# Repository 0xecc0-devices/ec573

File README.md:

# ec573 - Amiga 500 8MB Z2 DRAM + 2 channel IDE controller

## description
The ecc0 573 - or ec573 - is an Amiga 500 internal 8MB DRAM Zorro II expansion with 2 channel autoboot IDE controller sitting under the MC68000 CPU. It does fit into a standard Amiga 500 Mainboard interfering with neither ROM nor expansion connector.

### rendered pcb

### real pcb

### fitted into A500

DRAM and IDE controller are added using Amiga autoconfig mechanism with chain snooping. The expansion requires at least Kickstart 2.04 (v37.299).

## features

 - 8MB DRAM Zorro II memory expansion
  - IDE controller with 2 channels for 4 devices using the fabulous [lide.device](https://github.com/LIV2/lide.device)
 - full Zorro II autoconfig
 - jumperless
 - 2,5" IDE connector
 - 3,5" IDE connector with +5V power supply (fused on pin 20)
 - IDE LED connector
 - 128kB IDE controller ROM with CD boot capability
 - IDE autoboot ROM in circuit flash updateable
 - compatible with Kickstart v37.299 (2.04) and later

## technical details
 - 8MB DRAM mapped into Amiga's Zorro II memory address space ($20.0000 - $9F.FFFF)
 - 128kB IDE controller mapped as I/O device into Amiga's Zorro II I/O address space
 - 15,6 &#xb5;S DRAM CBR refresh

## limitations
The ecc0 573 has been designed to achieve several goals. This leaves the finished design with limitations which are intended, yet to be made transparent.

1. Due to the absense of Amiga Zorro Autoconfig signals **cfgin** and **cfgout** on the CPU slot, a snooping mechanism waits for all other devices to be configured first. This snooping mechanism needs at least Kickstart v37.299 to work.
2. Neither DRAM nor IDE controller are deactivateable.
3. The Zorro II DRAM size is fixed to 8MB. If another autoconfig device is claiming any memory before, none of the expansion's DRAM will be available.
4. The IDE controller uses [lide.device](https://github.com/LIV2/lide.device) by Matt Harlum as autoboot firmware thus inheriting all it's limitations.
5. The expansion always configures last in the autoconfiguration chain and uses the remaining resources available.
<!--stackedit_data:
eyJoaXN0b3J5IjpbMTAzMzAxODg2NSwtMTc1ODM2NjkzMCwxMD
k5NTEyNDgxXX0=
-->

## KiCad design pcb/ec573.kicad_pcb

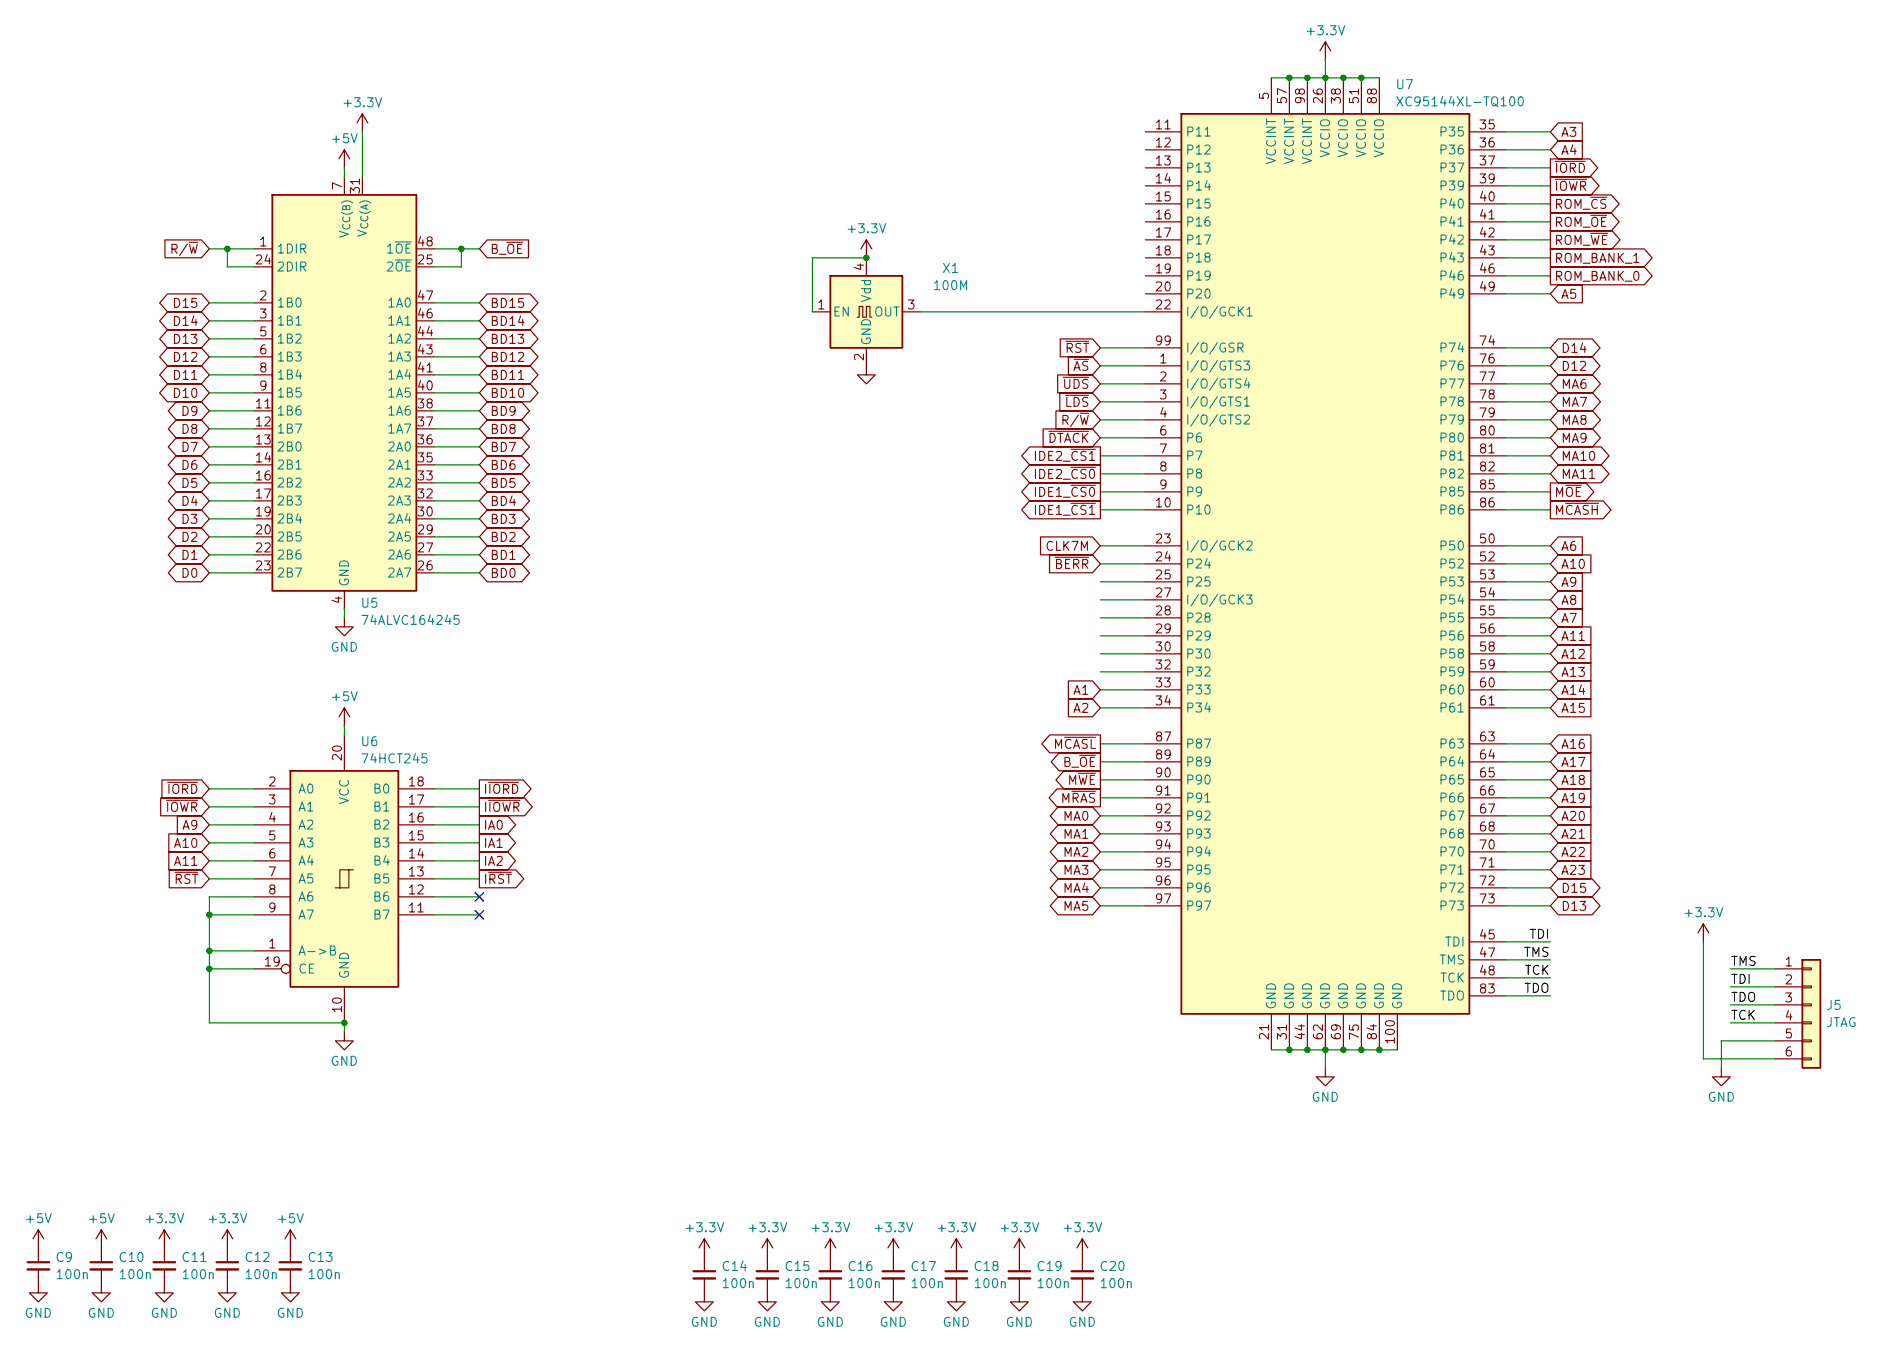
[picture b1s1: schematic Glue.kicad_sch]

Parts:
C9, C10, C11, C12, C13, C14, C15, C16, C17, C18, C19, C20: 100n; C_0603_1608Metric
J5: JTAG; PinHeader_1x06_P1.27mm_Vertical
U5: 74ALVC164245; TSSOP-48_6.1x12.5mm_P0.5mm
U6: 74HCT245; TSSOP-20_4.4x6.5mm_P0.65mm
U7: XC95144XL-TQ100; TQFP-100_14x14mm_P0.5mm
X1: 100M; Oscillator_SMD_Abracon_ASE-4Pin_3.2x2.5mm

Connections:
+3.3V: C11.1, C12.1, C14.1, C15.1, C16.1, C17.1, C18.1, C19.1, C20.1, J5.6, U5.31 (V_{CC(A)}), U5.42 (V_{CC(A)}), U7.5 (VCCINT), U7.26 (VCCIO), U7.38 (VCCIO), U7.51 (VCCIO), U7.57 (VCCINT), U7.88 (VCCIO), U7.98 (VCCINT), X1.1 (EN), X1.4 (Vdd); also elsewhere on the board
+5V: C9.1, C10.1, C13.1, U5.7 (V_{CC(B)}), U5.18 (V_{CC(B)}), U6.20 (VCC); also elsewhere on the board
/Glue/TCK: J5.4, U7.48 (TCK)
/Glue/TDI: J5.2, U7.45 (TDI)
/Glue/TDO: J5.3, U7.83 (TDO)
/Glue/TMS: J5.1, U7.47 (TMS)
A1: U7.33; also elsewhere on the board
A2: U7.34; also elsewhere on the board
A3: U7.35; also elsewhere on the board
A4: U7.36; also elsewhere on the board
A5: U7.49; also elsewhere on the board
A6: U7.50; also elsewhere on the board
A7: U7.55; also elsewhere on the board
A8: U7.54; also elsewhere on the board
A9: U6.4 (A2), U7.53; also elsewhere on the board
A10: U6.5 (A3), U7.52; also elsewhere on the board
A11: U6.6 (A4), U7.56; also elsewhere on the board
A12: U7.58; also elsewhere on the board
A13: U7.59; also elsewhere on the board
A14: U7.60; also elsewhere on the board
A15: U7.61; also elsewhere on the board
A16: U7.63; also elsewhere on the board
A17: U7.64; also elsewhere on the board
A18: U7.65; also elsewhere on the board
A19: U7.66; also elsewhere on the board
A20: U7.67; also elsewhere on the board
A21: U7.68; also elsewhere on the board
A22: U7.70; also elsewhere on the board
A23: U7.71; also elsewhere on the board
BD0: U5.26 (2A7); also elsewhere on the board
BD1: U5.27 (2A6); also elsewhere on the board
BD2: U5.29 (2A5); also elsewhere on the board
BD3: U5.30 (2A4); also elsewhere on the board
BD4: U5.32 (2A3); also elsewhere on the board
BD5: U5.33 (2A2); also elsewhere on the board
BD6: U5.35 (2A1); also elsewhere on the board
BD7: U5.36 (2A0); also elsewhere on the board
BD8: U5.37 (1A7); also elsewhere on the board
BD9: U5.38 (1A6); also elsewhere on the board
BD10: U5.40 (1A5); also elsewhere on the board
BD11: U5.41 (1A4); also elsewhere on the board
BD12: U5.43 (1A3); also elsewhere on the board
BD13: U5.44 (1A2); also elsewhere on the board
BD14: U5.46 (1A1); also elsewhere on the board
BD15: U5.47 (1A0); also elsewhere on the board
B_~OE: U5.25 (2~OE), U5.48 (1~OE), U7.89
CLK7M: U7.23 (I/O/GCK2); also elsewhere on the board
D0: U5.23 (2B7); also elsewhere on the board
D1: U5.22 (2B6); also elsewhere on the board
D2: U5.20 (2B5); also elsewhere on the board
D3: U5.19 (2B4); also elsewhere on the board
D4: U5.17 (2B3); also elsewhere on the board
D5: U5.16 (2B2); also elsewhere on the board
D6: U5.14 (2B1); also elsewhere on the board
D7: U5.13 (2B0); also elsewhere on the board
D8: U5.12 (1B7); also elsewhere on the board
D9: U5.11 (1B6); also elsewhere on the board
D10: U5.9 (1B5); also elsewhere on the board
D11: U5.8 (1B4); also elsewhere on the board
D12: U5.6 (1B3), U7.76; also elsewhere on the board
D13: U5.5 (1B2), U7.73; also elsewhere on the board
D14: U5.3 (1B1), U7.74; also elsewhere on the board
D15: U5.2 (1B0), U7.72; also elsewhere on the board
GND: C9.2, C10.2, C11.2, C12.2, C13.2, C14.2, C15.2, C16.2, C17.2, C18.2, C19.2, C20.2, J5.5, U5.4 (GND), U5.10 (GND), U5.15 (GND), U5.21 (GND), U5.28 (GND), U5.34 (GND), U5.39 (GND), U5.45 (GND), U6.1 (A->B), U6.8 (A6), U6.9 (A7), U6.10 (GND), U6.19 (CE), U7.21 (GND), U7.31 (GND), U7.44 (GND), U7.62 (GND), U7.69 (GND), U7.75 (GND), U7.84 (GND), U7.100 (GND), X1.2 (GND); also elsewhere on the board
IA0: U6.16 (B2); also elsewhere on the board
IA1: U6.15 (B3); also elsewhere on the board
IA2: U6.14 (B4); also elsewhere on the board
IDE1_~CS0: U7.9; also elsewhere on the board
IDE1_~CS1: U7.10; also elsewhere on the board
IDE2_~CS0: U7.8; also elsewhere on the board
IDE2_~CS1: U7.7; also elsewhere on the board
I~IORD: U6.18 (B0); also elsewhere on the board
I~IOWR: U6.17 (B1); also elsewhere on the board
I~RST: U6.13 (B5); also elsewhere on the board
MA0: U7.92; also elsewhere on the board
MA1: U7.93; also elsewhere on the board
MA2: U7.94; also elsewhere on the board
MA3: U7.95; also elsewhere on the board
MA4: U7.96; also elsewhere on the board
MA5: U7.97; also elsewhere on the board
MA6: U7.77; also elsewhere on the board
MA7: U7.78; also elsewhere on the board
MA8: U7.79; also elsewhere on the board
MA9: U7.80; also elsewhere on the board
MA10: U7.81; also elsewhere on the board
MA11: U7.82; also elsewhere on the board
M~CASH: U7.86; also elsewhere on the board
M~CASL: U7.87; also elsewhere on the board
M~OE: U7.85; also elsewhere on the board
M~RAS: U7.91; also elsewhere on the board
M~WE: U7.90; also elsewhere on the board
unnamed: U7.22 (I/O/GCK1), X1.3 (OUT)
ROM_BANK_0: U7.46; also elsewhere on the board
ROM_BANK_1: U7.43; also elsewhere on the board
ROM_~CS: U7.40; also elsewhere on the board
ROM_~OE: U7.41; also elsewhere on the board
ROM_~WE: U7.42; also elsewhere on the board
R/~W: U5.1 (1DIR), U5.24 (2DIR), U7.4 (I/O/GTS2); also elsewhere on the board
~AS: U7.1 (I/O/GTS3); also elsewhere on the board
~BERR: U7.24; also elsewhere on the board
~DTACK: U7.6; also elsewhere on the board
~IORD: U6.2 (A0), U7.37
~IOWR: U6.3 (A1), U7.39
~LDS: U7.3 (I/O/GTS1); also elsewhere on the board
~RST: U6.7 (A5), U7.99 (I/O/GSR); also elsewhere on the board
~UDS: U7.2 (I/O/GTS4); also elsewhere on the board

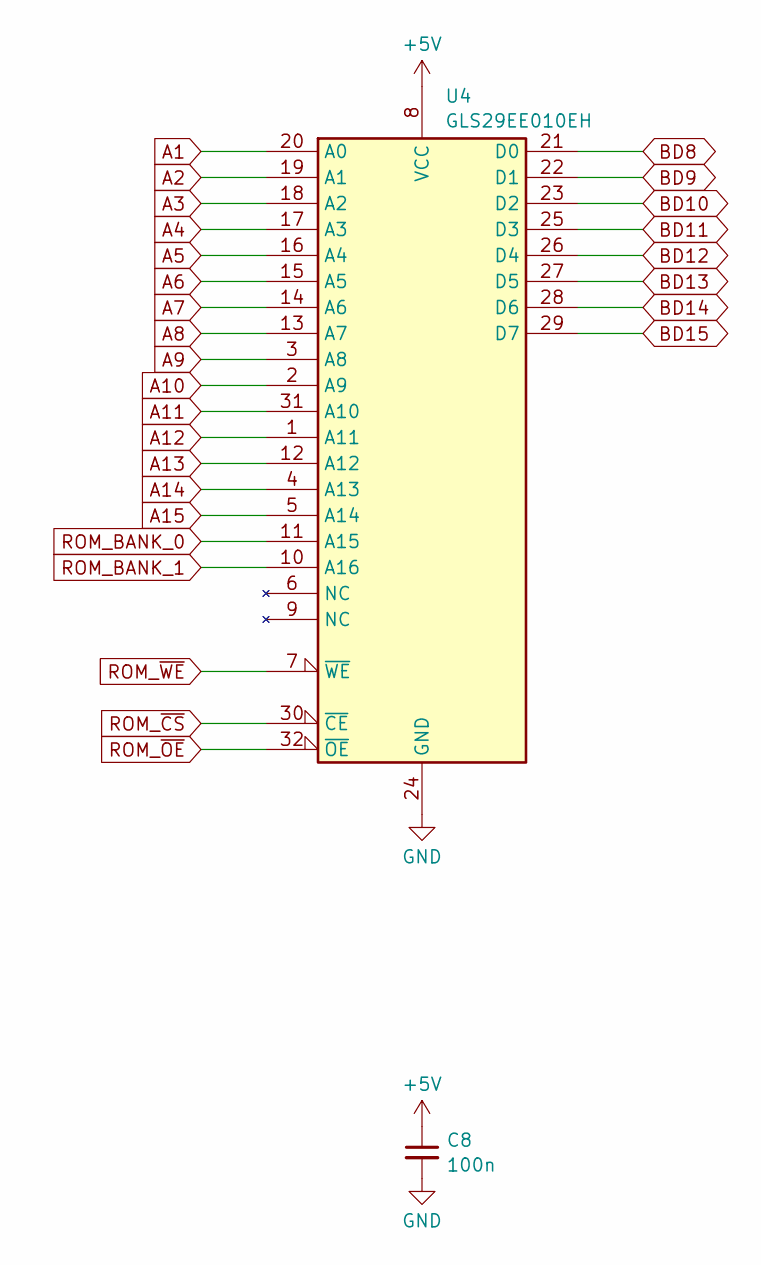
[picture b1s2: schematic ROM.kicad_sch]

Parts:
C8: 100n; C_0603_1608Metric
U4: GLS29EE010EH; TSOP-I-32_18.4x8mm_P0.5mm

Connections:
+5V: C8.1, U4.8 (VCC); also elsewhere on the board
A1: U4.20 (A0); also elsewhere on the board
A2: U4.19 (A1); also elsewhere on the board
A3: U4.18 (A2); also elsewhere on the board
A4: U4.17 (A3); also elsewhere on the board
A5: U4.16 (A4); also elsewhere on the board
A6: U4.15 (A5); also elsewhere on the board
A7: U4.14 (A6); also elsewhere on the board
A8: U4.13 (A7); also elsewhere on the board
A9: U4.3 (A8); also elsewhere on the board
A10: U4.2 (A9); also elsewhere on the board
A11: U4.31 (A10); also elsewhere on the board
A12: U4.1 (A11); also elsewhere on the board
A13: U4.12 (A12); also elsewhere on the board
A14: U4.4 (A13); also elsewhere on the board
A15: U4.5 (A14); also elsewhere on the board
BD8: U4.21 (D0); also elsewhere on the board
BD9: U4.22 (D1); also elsewhere on the board
BD10: U4.23 (D2); also elsewhere on the board
BD11: U4.25 (D3); also elsewhere on the board
BD12: U4.26 (D4); also elsewhere on the board
BD13: U4.27 (D5); also elsewhere on the board
BD14: U4.28 (D6); also elsewhere on the board
BD15: U4.29 (D7); also elsewhere on the board
GND: C8.2, U4.24 (GND); also elsewhere on the board
ROM_BANK_0: U4.11 (A15); also elsewhere on the board
ROM_BANK_1: U4.10 (A16); also elsewhere on the board
ROM_~CS: U4.30 (~CE); also elsewhere on the board
ROM_~OE: U4.32 (~OE); also elsewhere on the board
ROM_~WE: U4.7 (~WE); also elsewhere on the board

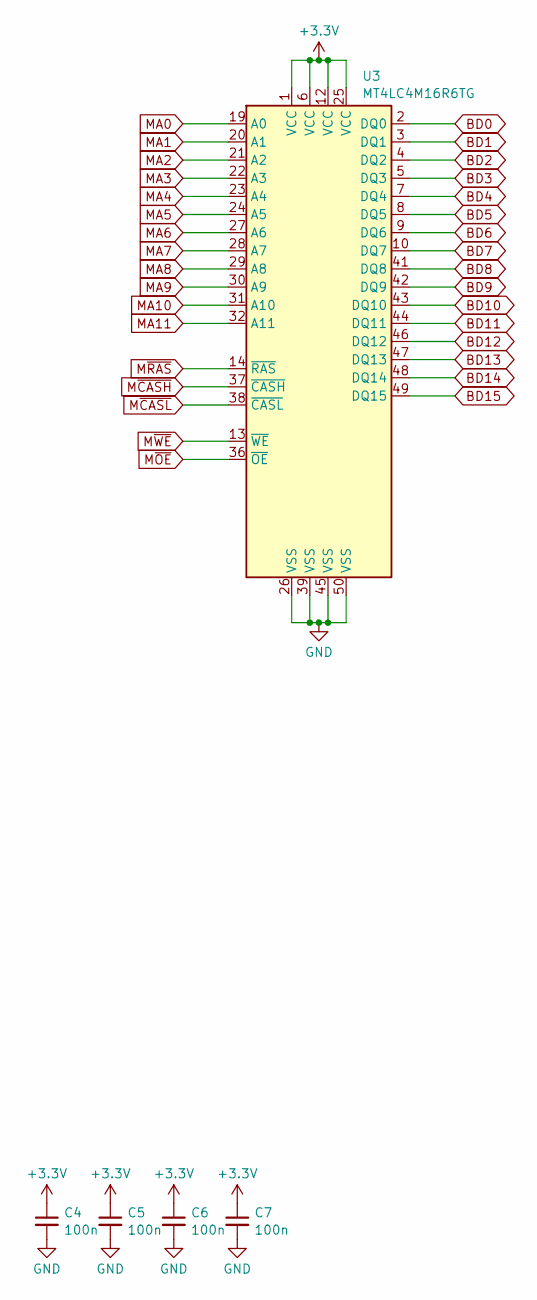
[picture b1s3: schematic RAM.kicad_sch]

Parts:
C4, C5, C6, C7: 100n; C_0603_1608Metric
U3: MT4LC4M16R6TG; TSOP-II-50_20.86x10.16mm_P0.8mm

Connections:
+3.3V: C4.1, C5.1, C6.1, C7.1, U3.1 (VCC), U3.6 (VCC), U3.12 (VCC), U3.25 (VCC); also elsewhere on the board
BD0: U3.2 (DQ0); also elsewhere on the board
BD1: U3.3 (DQ1); also elsewhere on the board
BD2: U3.4 (DQ2); also elsewhere on the board
BD3: U3.5 (DQ3); also elsewhere on the board
BD4: U3.7 (DQ4); also elsewhere on the board
BD5: U3.8 (DQ5); also elsewhere on the board
BD6: U3.9 (DQ6); also elsewhere on the board
BD7: U3.10 (DQ7); also elsewhere on the board
BD8: U3.41 (DQ8); also elsewhere on the board
BD9: U3.42 (DQ9); also elsewhere on the board
BD10: U3.43 (DQ10); also elsewhere on the board
BD11: U3.44 (DQ11); also elsewhere on the board
BD12: U3.46 (DQ12); also elsewhere on the board
BD13: U3.47 (DQ13); also elsewhere on the board
BD14: U3.48 (DQ14); also elsewhere on the board
BD15: U3.49 (DQ15); also elsewhere on the board
GND: C4.2, C5.2, C6.2, C7.2, U3.26 (VSS), U3.39 (VSS), U3.45 (VSS), U3.50 (VSS); also elsewhere on the board
MA0: U3.19 (A0); also elsewhere on the board
MA1: U3.20 (A1); also elsewhere on the board
MA2: U3.21 (A2); also elsewhere on the board
MA3: U3.22 (A3); also elsewhere on the board
MA4: U3.23 (A4); also elsewhere on the board
MA5: U3.24 (A5); also elsewhere on the board
MA6: U3.27 (A6); also elsewhere on the board
MA7: U3.28 (A7); also elsewhere on the board
MA8: U3.29 (A8); also elsewhere on the board
MA9: U3.30 (A9); also elsewhere on the board
MA10: U3.31 (A10); also elsewhere on the board
MA11: U3.32 (A11); also elsewhere on the board
M~CASH: U3.37 (~CASH); also elsewhere on the board
M~CASL: U3.38 (~CASL); also elsewhere on the board
M~OE: U3.36 (~OE); also elsewhere on the board
M~RAS: U3.14 (~RAS); also elsewhere on the board
M~WE: U3.13 (~WE); also elsewhere on the board

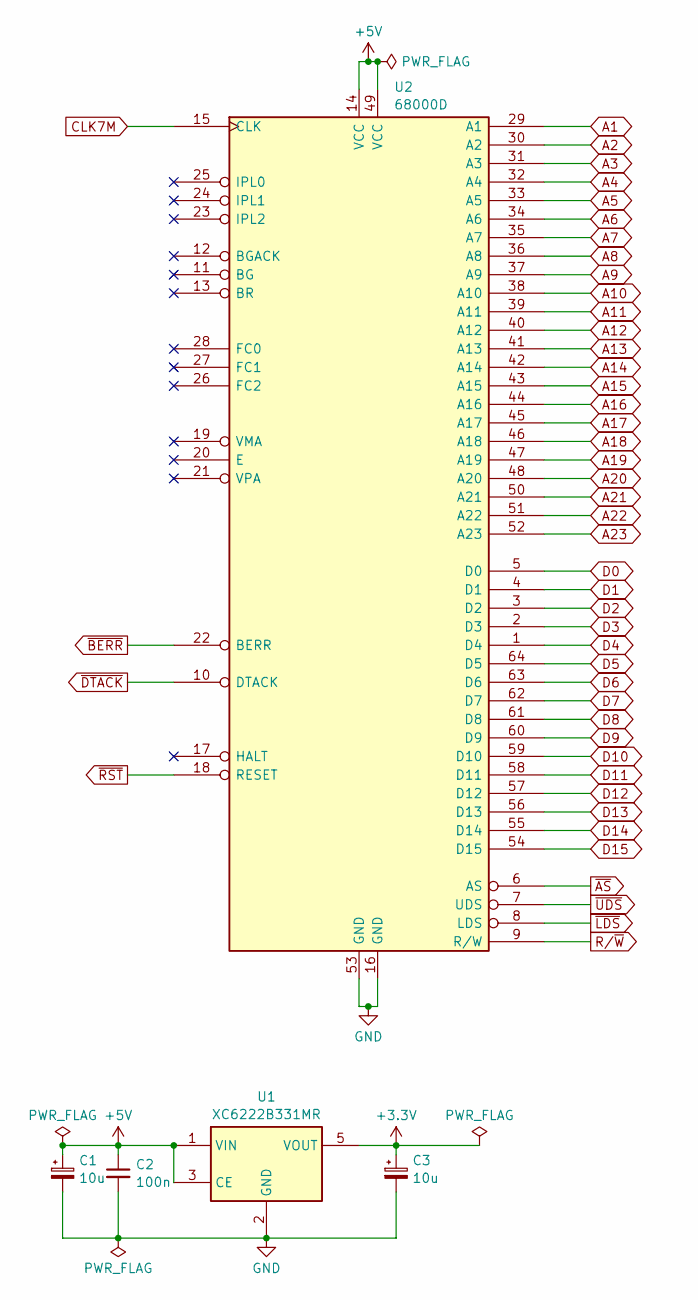
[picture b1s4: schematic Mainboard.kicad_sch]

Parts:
C1, C3: 10u; CP_EIA-3216-10_Kemet-I
C2: 100n; C_0603_1608Metric
U1: XC6222B331MR; SOT-23-5
U2: 68000D; DIP-64_W22.86mm_LongPads

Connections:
+3.3V: C3.1, U1.5 (VOUT); also elsewhere on the board
+5V: C1.1, C2.1, U1.1 (VIN), U1.3 (CE), U2.14 (VCC), U2.49 (VCC); also elsewhere on the board
A1: U2.29 (A1); also elsewhere on the board
A2: U2.30 (A2); also elsewhere on the board
A3: U2.31 (A3); also elsewhere on the board
A4: U2.32 (A4); also elsewhere on the board
A5: U2.33 (A5); also elsewhere on the board
A6: U2.34 (A6); also elsewhere on the board
A7: U2.35 (A7); also elsewhere on the board
A8: U2.36 (A8); also elsewhere on the board
A9: U2.37 (A9); also elsewhere on the board
A10: U2.38 (A10); also elsewhere on the board
A11: U2.39 (A11); also elsewhere on the board
A12: U2.40 (A12); also elsewhere on the board
A13: U2.41 (A13); also elsewhere on the board
A14: U2.42 (A14); also elsewhere on the board
A15: U2.43 (A15); also elsewhere on the board
A16: U2.44 (A16); also elsewhere on the board
A17: U2.45 (A17); also elsewhere on the board
A18: U2.46 (A18); also elsewhere on the board
A19: U2.47 (A19); also elsewhere on the board
A20: U2.48 (A20); also elsewhere on the board
A21: U2.50 (A21); also elsewhere on the board
A22: U2.51 (A22); also elsewhere on the board
A23: U2.52 (A23); also elsewhere on the board
CLK7M: U2.15 (CLK); also elsewhere on the board
D0: U2.5 (D0); also elsewhere on the board
D1: U2.4 (D1); also elsewhere on the board
D2: U2.3 (D2); also elsewhere on the board
D3: U2.2 (D3); also elsewhere on the board
D4: U2.1 (D4); also elsewhere on the board
D5: U2.64 (D5); also elsewhere on the board
D6: U2.63 (D6); also elsewhere on the board
D7: U2.62 (D7); also elsewhere on the board
D8: U2.61 (D8); also elsewhere on the board
D9: U2.60 (D9); also elsewhere on the board
D10: U2.59 (D10); also elsewhere on the board
D11: U2.58 (D11); also elsewhere on the board
D12: U2.57 (D12); also elsewhere on the board
D13: U2.56 (D13); also elsewhere on the board
D14: U2.55 (D14); also elsewhere on the board
D15: U2.54 (D15); also elsewhere on the board
GND: C1.2, C2.2, C3.2, U1.2 (GND), U2.16 (GND), U2.53 (GND); also elsewhere on the board
R/~W: U2.9 (R/W); also elsewhere on the board
~AS: U2.6 (AS); also elsewhere on the board
~BERR: U2.22 (BERR); also elsewhere on the board
~DTACK: U2.10 (DTACK); also elsewhere on the board
~LDS: U2.8 (LDS); also elsewhere on the board
~RST: U2.18 (RESET); also elsewhere on the board
~UDS: U2.7 (UDS); also elsewhere on the board

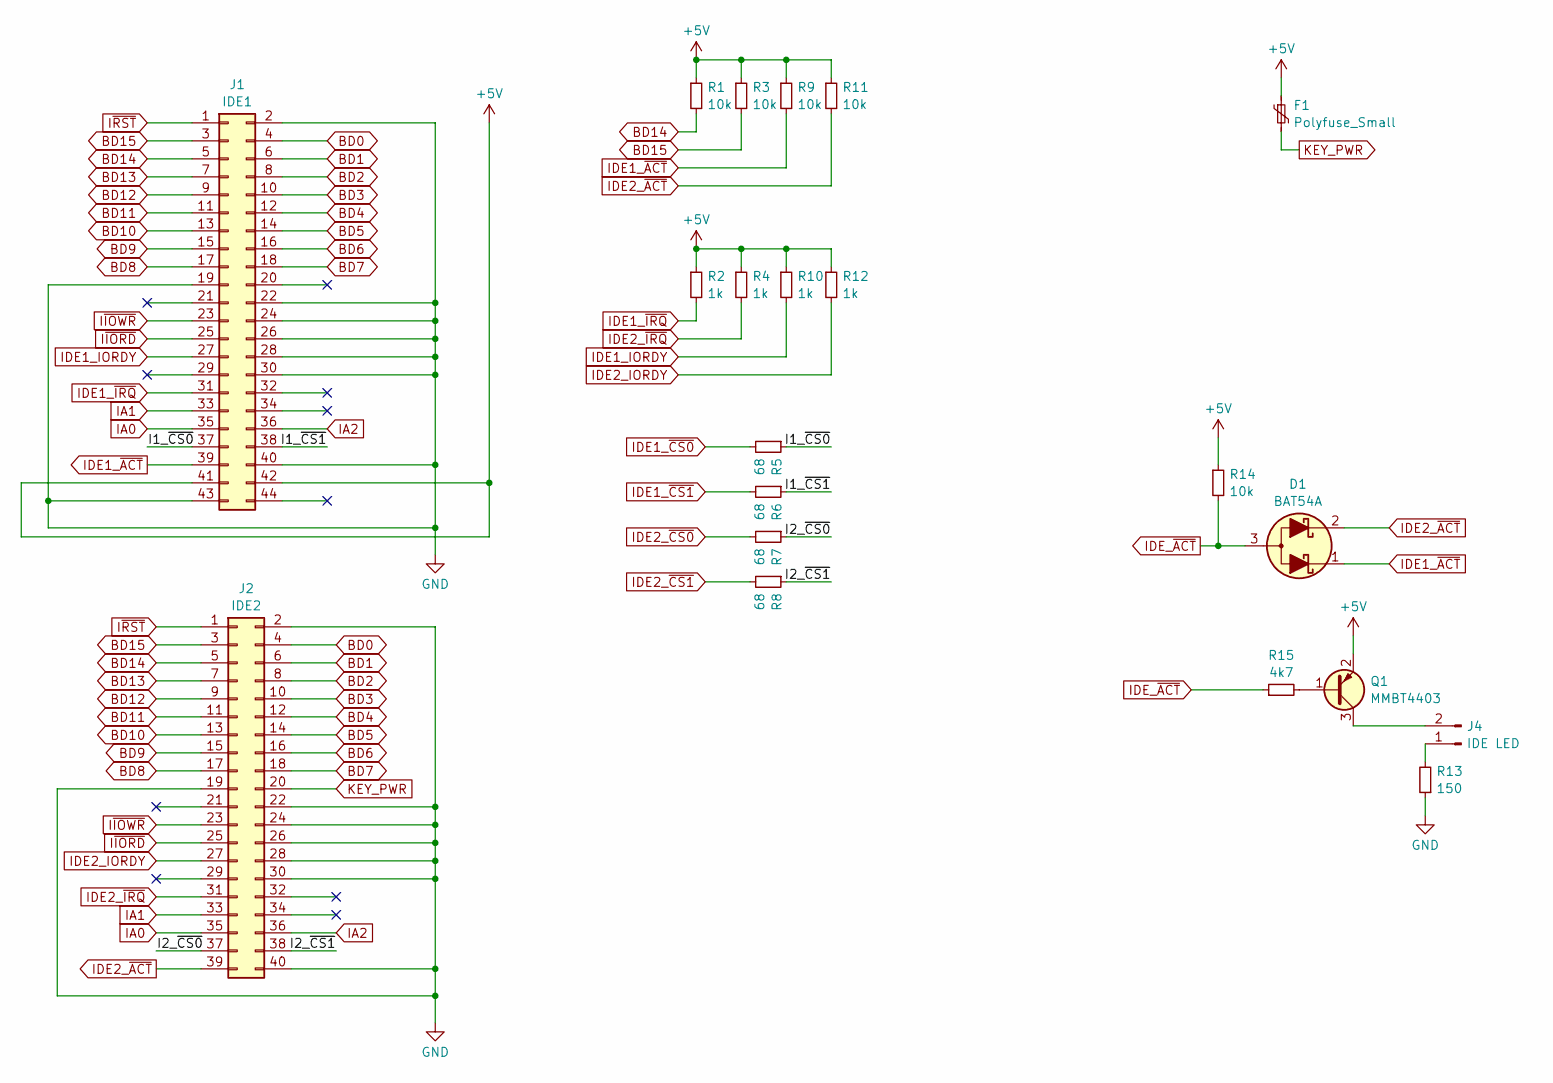
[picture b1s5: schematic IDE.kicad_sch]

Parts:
D1: BAT54A; SOT-23
F1: Polyfuse_Small; Fuse_0805_2012Metric
J1: IDE1; PinHeader_2x22_P2.00mm_Vertical
J2: IDE2; PinHeader_2x20_P2.54mm_Vertical
J4: IDE LED; PinHeader_1x02_P2.54mm_Vertical
Q1: MMBT4403; SOT-23
R1, R3, R9, R11, R14: 10k; R_0603_1608Metric
R2, R4, R10, R12: 1k; R_0603_1608Metric
R5, R6, R7, R8: 68; R_0603_1608Metric
R13: 150; R_0603_1608Metric
R15: 4k7; R_0603_1608Metric

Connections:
+5V: F1.1, J1.41, J1.42, Q1.2 (E), R1.1, R2.1, R3.1, R4.1, R9.1, R10.1, R11.1, R12.1, R14.1; also elsewhere on the board
/IDE/I1_~CS0: J1.37, R5.1
/IDE/I1_~CS1: J1.38, R6.1
/IDE/I2_~CS0: J2.37, R7.1
/IDE/I2_~CS1: J2.38, R8.1
BD0: J1.4, J2.4; also elsewhere on the board
BD1: J1.6, J2.6; also elsewhere on the board
BD2: J1.8, J2.8; also elsewhere on the board
BD3: J1.10, J2.10; also elsewhere on the board
BD4: J1.12, J2.12; also elsewhere on the board
BD5: J1.14, J2.14; also elsewhere on the board
BD6: J1.16, J2.16; also elsewhere on the board
BD7: J1.18, J2.18; also elsewhere on the board
BD8: J1.17, J2.17; also elsewhere on the board
BD9: J1.15, J2.15; also elsewhere on the board
BD10: J1.13, J2.13; also elsewhere on the board
BD11: J1.11, J2.11; also elsewhere on the board
BD12: J1.9, J2.9; also elsewhere on the board
BD13: J1.7, J2.7; also elsewhere on the board
BD14: J1.5, J2.5, R1.2; also elsewhere on the board
BD15: J1.3, J2.3, R3.2; also elsewhere on the board
GND: J1.2, J1.19, J1.22, J1.24, J1.26, J1.28, J1.30, J1.40, J1.43, J2.2, J2.19, J2.22, J2.24, J2.26, J2.28, J2.30, J2.40, R13.1; also elsewhere on the board
IA0: J1.35, J2.35; also elsewhere on the board
IA1: J1.33, J2.33; also elsewhere on the board
IA2: J1.36, J2.36; also elsewhere on the board
IDE1_IORDY: J1.27, R10.2
IDE1_~ACT: D1.1 (K1), J1.39, R9.2
IDE1_~CS0: R5.2; also elsewhere on the board
IDE1_~CS1: R6.2; also elsewhere on the board
IDE1_~IRQ: J1.31, R2.2
IDE2_IORDY: J2.27, R12.2
IDE2_~ACT: D1.2 (K2), J2.39, R11.2
IDE2_~CS0: R7.2; also elsewhere on the board
IDE2_~CS1: R8.2; also elsewhere on the board
IDE2_~IRQ: J2.31, R4.2
IDE_~ACT: D1.3 (A), R14.2, R15.1
I~IORD: J1.25, J2.25; also elsewhere on the board
I~IOWR: J1.23, J2.23; also elsewhere on the board
I~RST: J1.1, J2.1; also elsewhere on the board
KEY_PWR: F1.2, J2.20
unnamed: J4.1, R13.2
unnamed: J4.2, Q1.3 (C)
unnamed: Q1.1 (B), R15.2

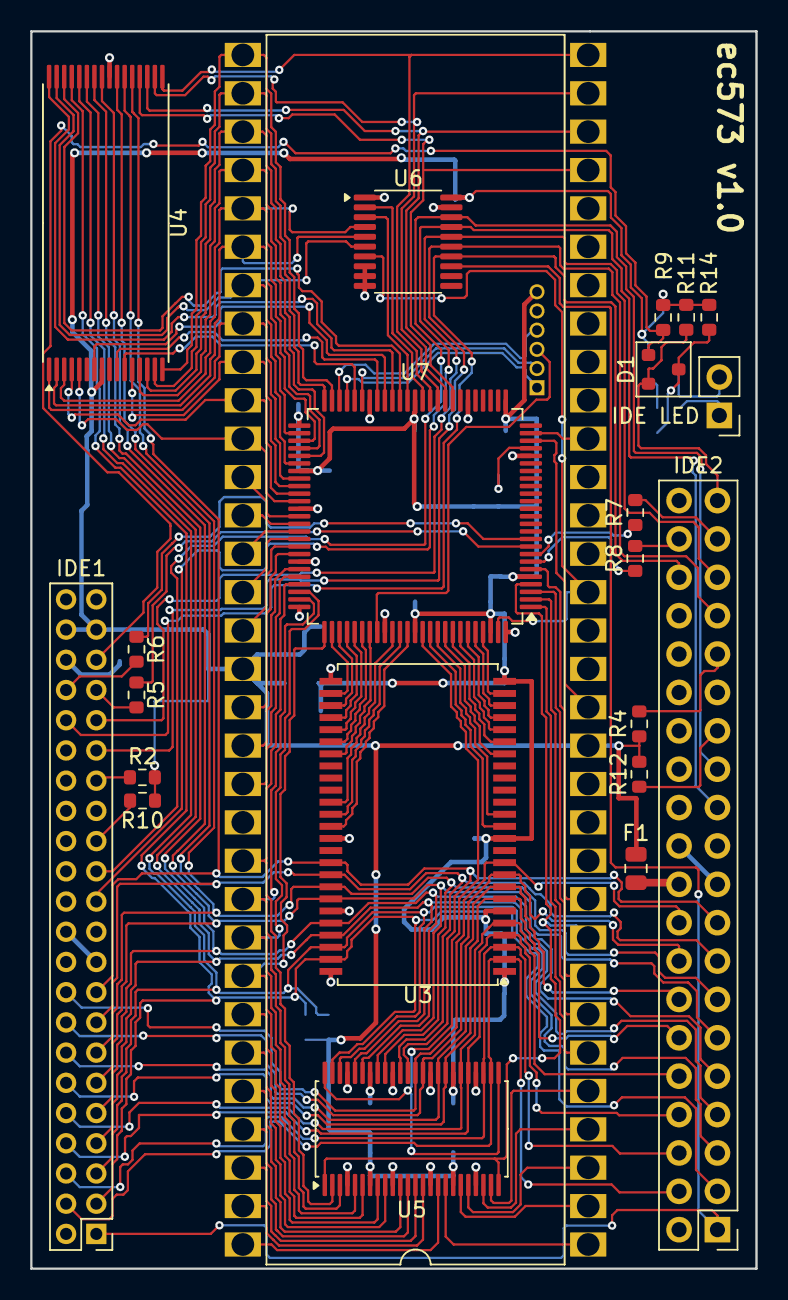
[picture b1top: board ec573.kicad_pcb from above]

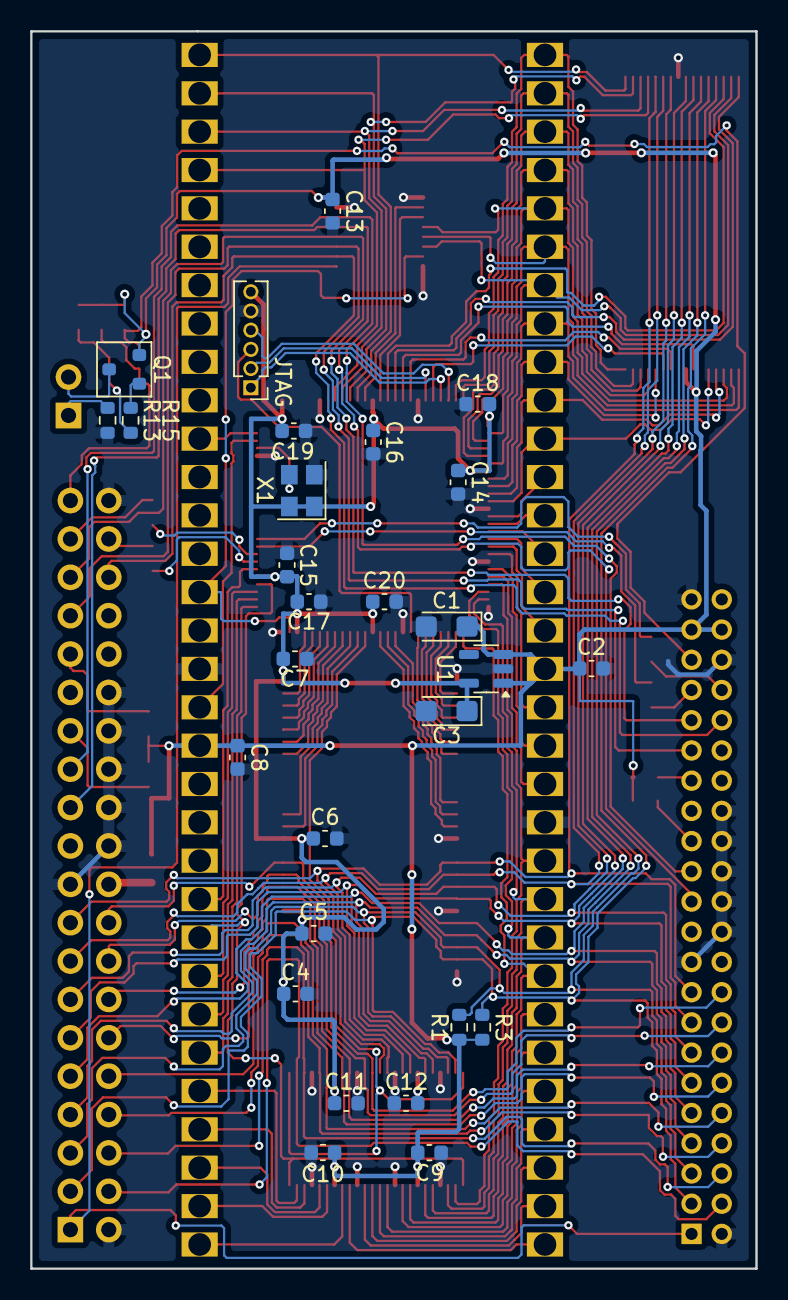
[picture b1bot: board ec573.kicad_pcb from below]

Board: 2 copper layers, 48.0 x 81.9 mm, 50 parts (28 on the bottom side), 121 nets.

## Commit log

2026-06-21 README.md updated from https://stackedit.io/
2026-06-21 added pictures of built hardware
2026-06-21 changed orientation of picture
